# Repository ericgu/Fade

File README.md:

# Fade - a ESP32 Animation System

Fade is an ESP32-based animation system. It can drive WS2812/Neopixel addressable LEDs, PWM-based devices (LEDs or anything else that supports PWM), and hobby servo motors. 

## Introduction

See the introduction video [here](https://www.youtube.com/watch?v=-CXQz1x2k9o).

## Getting Started (Windows)

### Copy the installation files to a local directory

The installation files can be found [here](https://github.com/ericgu/Fade/tree/master/InstallFiles).

### Install WinFade
Run WinFadeInstaller.msi

### Install python and esptool.py

These tools will be used to copy the Fade system onto the ESP32

[How to Install Esptool on Windows 10](https://cyberblogspot.com/how-to-install-esptool-on-windows-10/)

### Copy/Flash the software onto the ESP32

It's good to have experience copying programs to the ESP32 from the Arduino IDE or another IDE before you try this. 

1. Connect the ESP to the computer with a USB cable (or whatever programmer you use).
2. Determine what COM port you are connected to
3. Edit FlashToEsp32.bat to specify the proper COM port
4. Run FlashToEsp32.bat
5. Put the ESP board into download board (press and hold the program button or press and hold it and then press and release the reset button)
6. Watch the download progress. 

### Verify the installation

1. Connect to the COM port with a terminal program such as CoolTerm.
2. Reset the ESP32
3. You should see debug text that says "Configuring Access Point"

### Connect the ESP to your wireless network

1. Using a wireless device (laptop or phone), connect to a network with the SSID named "FadeController_<number", password "12345678"
2. Your browser may hit the page directly; if not, navigate to [http://192.168.4.1](http://192.168.4.1)
3. Choose the appropriate wireless network. 
4. Reset the ESP

### Connect to the Fade web page

1. Determine the IP address of the ESP. You can get that either from your router or from the debug messages written when the ESP boots.
2. Enter that IP address into your web browser.
3. That should give you the web-based IDE for the ESP. 

### Connect WinFade to the ESP

1. Enter the IP address of the ESP into WinFade.
2. Enjoy.

## Fade language details

[Tutorial](https://rawcdn.githack.com/ericgu/Fade/26681499a88c3c0935cea77f8de56b3fef22759a/docs/FadeLanguageTutorial.html)
[Language Reference](https://rawcdn.githack.com/ericgu/Fade/26681499a88c3c0935cea77f8de56b3fef22759a/docs/FadeLanguageReference.html)

# Sample code

See the FadeExamples directory

# Release Notes

9/10/2021

Finished support for remoting. This allows one ESP to drive multiple ESPs. There is a new LED type ("UdpSender") that will take commands for a specific of channels (LEDs or servos) and send them out over the local network using UDP. The remote ESPs use the "UdpReceiver" type to take those commands and send them to the local hardware.

This is for two primary scenarios: if you wanted to use more than 16 servos in a project, you can set up a remote ESP (or ESPs) and get a multiple of 16 servos. Also, it supports animations across multiple physical instances using a single set of driving code. 

In addition, if you want to run code on a computer or laptop and use that to drive the remotes, that is also possible. I've implemented that as a feature in WinFade; you can write your code there and see how it will run on the live remote hardware without having to download the code there. Not sure how much utility there is in that, but it allowed me to easily test the UdpReceiver code that runs on the ESP.

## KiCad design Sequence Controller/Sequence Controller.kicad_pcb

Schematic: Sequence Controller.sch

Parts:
ExtIn1: Conn_01x09_Male; Pin_Header_Straight_1x09_Pitch2.54mm
ExtOut1: Conn_01x09_Male; Pin_Header_Straight_1x09_Pitch2.54mm
J1: Conn_01x11_Male; Pin_Header_Straight_1x11_Pitch2.54mm
Q1, Q2, Q3, Q4, Q5, Q6, Q7, Q8: BSR202N; SOT-23
U1: ESP32Devkit30; Esp32_30_Pin

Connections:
/GND: ExtIn1.9, ExtOut1.9, J1.2, J1.3, Q1.2 (S), Q2.2 (S), Q3.2 (S), Q4.2 (S), Q5.2 (S), Q6.2 (S), Q7.2 (S), Q8.2 (S), U1.14, U1.17
unnamed: ExtIn1.1, Q1.1 (G), U1.30
unnamed: ExtIn1.2, Q2.1 (G), U1.29
unnamed: ExtIn1.3, Q3.1 (G), U1.26
unnamed: ExtIn1.4, Q4.1 (G), U1.25
unnamed: ExtIn1.5, Q5.1 (G), U1.24
unnamed: ExtIn1.6, Q6.1 (G), U1.23
unnamed: ExtIn1.7, Q7.1 (G), U1.20
unnamed: ExtIn1.8, Q8.1 (G), U1.19
unnamed: ExtOut1.1, U1.13
unnamed: ExtOut1.2, U1.12
unnamed: ExtOut1.3, U1.6
unnamed: ExtOut1.4, U1.7
unnamed: ExtOut1.5, U1.8
unnamed: ExtOut1.6, U1.9
unnamed: ExtOut1.7, U1.10
unnamed: ExtOut1.8, U1.11
unnamed: J1.1, U1.15
unnamed: J1.4, Q1.3 (D)
unnamed: J1.5, Q2.3 (D)
unnamed: J1.6, Q3.3 (D)
unnamed: J1.7, Q4.3 (D)
unnamed: J1.8, Q5.3 (D)
unnamed: J1.9, Q6.3 (D)
unnamed: J1.10, Q7.3 (D)
unnamed: J1.11, Q8.3 (D)

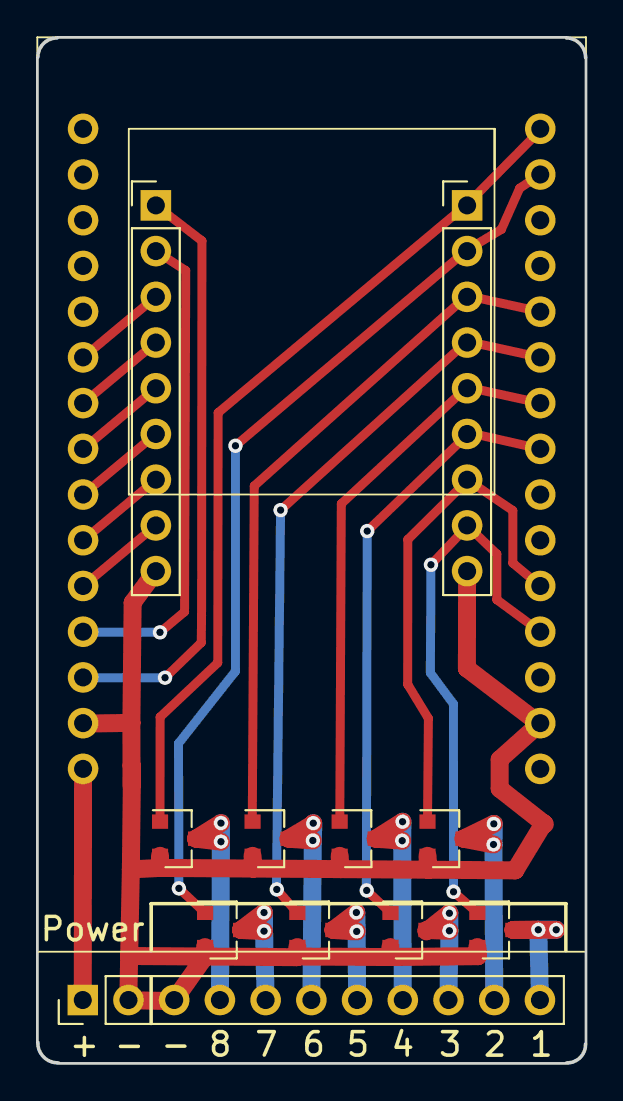
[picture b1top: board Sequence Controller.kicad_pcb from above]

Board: 2 copper layers, 30.4 x 57.0 mm, 12 parts (0 on the bottom side), 26 nets.

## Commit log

2019-07-30 initial
2019-09-08 new design, new code
2019-09-10 Version 1.0
2019-09-15 New command format, first try at wireless
2019-09-24 Named variables
2019-09-28 Changed LOOP to FOR
2019-10-10 added error reporting
2019-10-11 Finished error reporting...
2019-10-16 Added supervisor, refactored
2019-10-16 Modify settings to do startup on Init instead of constructor
2019-10-21 Added in node naming.
2019-12-03 Updated to support 1024 lines of code
2019-12-17 added method calls
2019-12-30 Restructure execution, add parameters!
2020-01-03 expressions!!!
2020-01-03 Removed old parsing and command result approach
2020-01-07 Switched to built-in commands
2020-01-29 expressions up and running...
2020-03-06 added multi-value variables
2020-03-06 builds in esp32 project now
2020-04-04 Working execution and delay
2020-04-08 New startup logic
2020-04-09 Config led type and count from code...
2020-04-14 New stuff...
2020-04-14 All tests pass using new evaluator
2020-04-15 Removed old expression code, fixed execution
2020-04-15 CommandSource uses incremental parsing
2020-04-15 Switched stack/variables to use execution context
2020-04-16 Copy constructor written...
2020-04-16 Tests up and running, verified on ESP
2020-04-16 Dynamic size based on # of leds is done
2020-04-16 General cleanup & renaming
2020-04-19 Added statement parsing
2020-04-19 tests
2020-04-20 New function calls working and fully tested
2020-04-21 Fixed save/restore of position issues
2020-04-21 RD parser up and functional...
2020-05-10 New variable scheme, tuned and polished
2020-05-11 new files
2020-08-28 Added button and BREAK support
2020-08-30 support multiple LED types, added button configuration
2020-08-31 small changes
2020-09-05 updated touch code
2020-09-15 Fixed multi-group LEDs, added DEBUG
2020-10-20 switched to hard reset after program update
2020-10-20 added string interning classes, not yet integrated
2020-12-22 New dynamic vector class
2020-12-22 Added environment class
2020-12-24 Switched system to use Vector for Variable data storage
2020-12-24 First array referencing tests
2020-12-28 Small fixes + warning fixes
2020-12-29 Modified to use ExpressionResult
2020-12-30 array indexes as l values work
2020-12-31 Added complex test, fixed error checking
2021-05-26 WinFade
2021-06-07 First version
2021-06-13 before rename
2021-06-13 Before statements
2021-06-13 func
2021-06-13 else, elseif
2021-06-13 return, break
2021-06-20 working before new vector allocation
2021-06-20 Free list for vector values
2021-06-22 linked list variable data management
2021-07-03 Fixed intellisense, etc.
2021-07-08 updated to do WS2812 teardown
2021-07-08 test
2021-07-11 create/delete RGB string support
2021-08-12 Added installer, release locations
2021-08-26 readme
2021-08-29 Added directions to use esptool.py to flash
2021-08-29 Updated installation code and directions
2021-08-30 Fix broken PWM
2021-09-01 Added servo support!
2021-09-07 first round UDP Sender
2021-09-07 LedType type
2021-09-10 UDP remoting works on ESP and in WinFade
2021-09-10 updated docs for remoting
2021-09-10 Modified LedConfig to take up to 16 parameters for PWM and servo
2021-09-10 Added fade sample code
2022-02-10 Lots of changes.
2022-12-11 Memory optimization to run garage animation + optimized string interning
